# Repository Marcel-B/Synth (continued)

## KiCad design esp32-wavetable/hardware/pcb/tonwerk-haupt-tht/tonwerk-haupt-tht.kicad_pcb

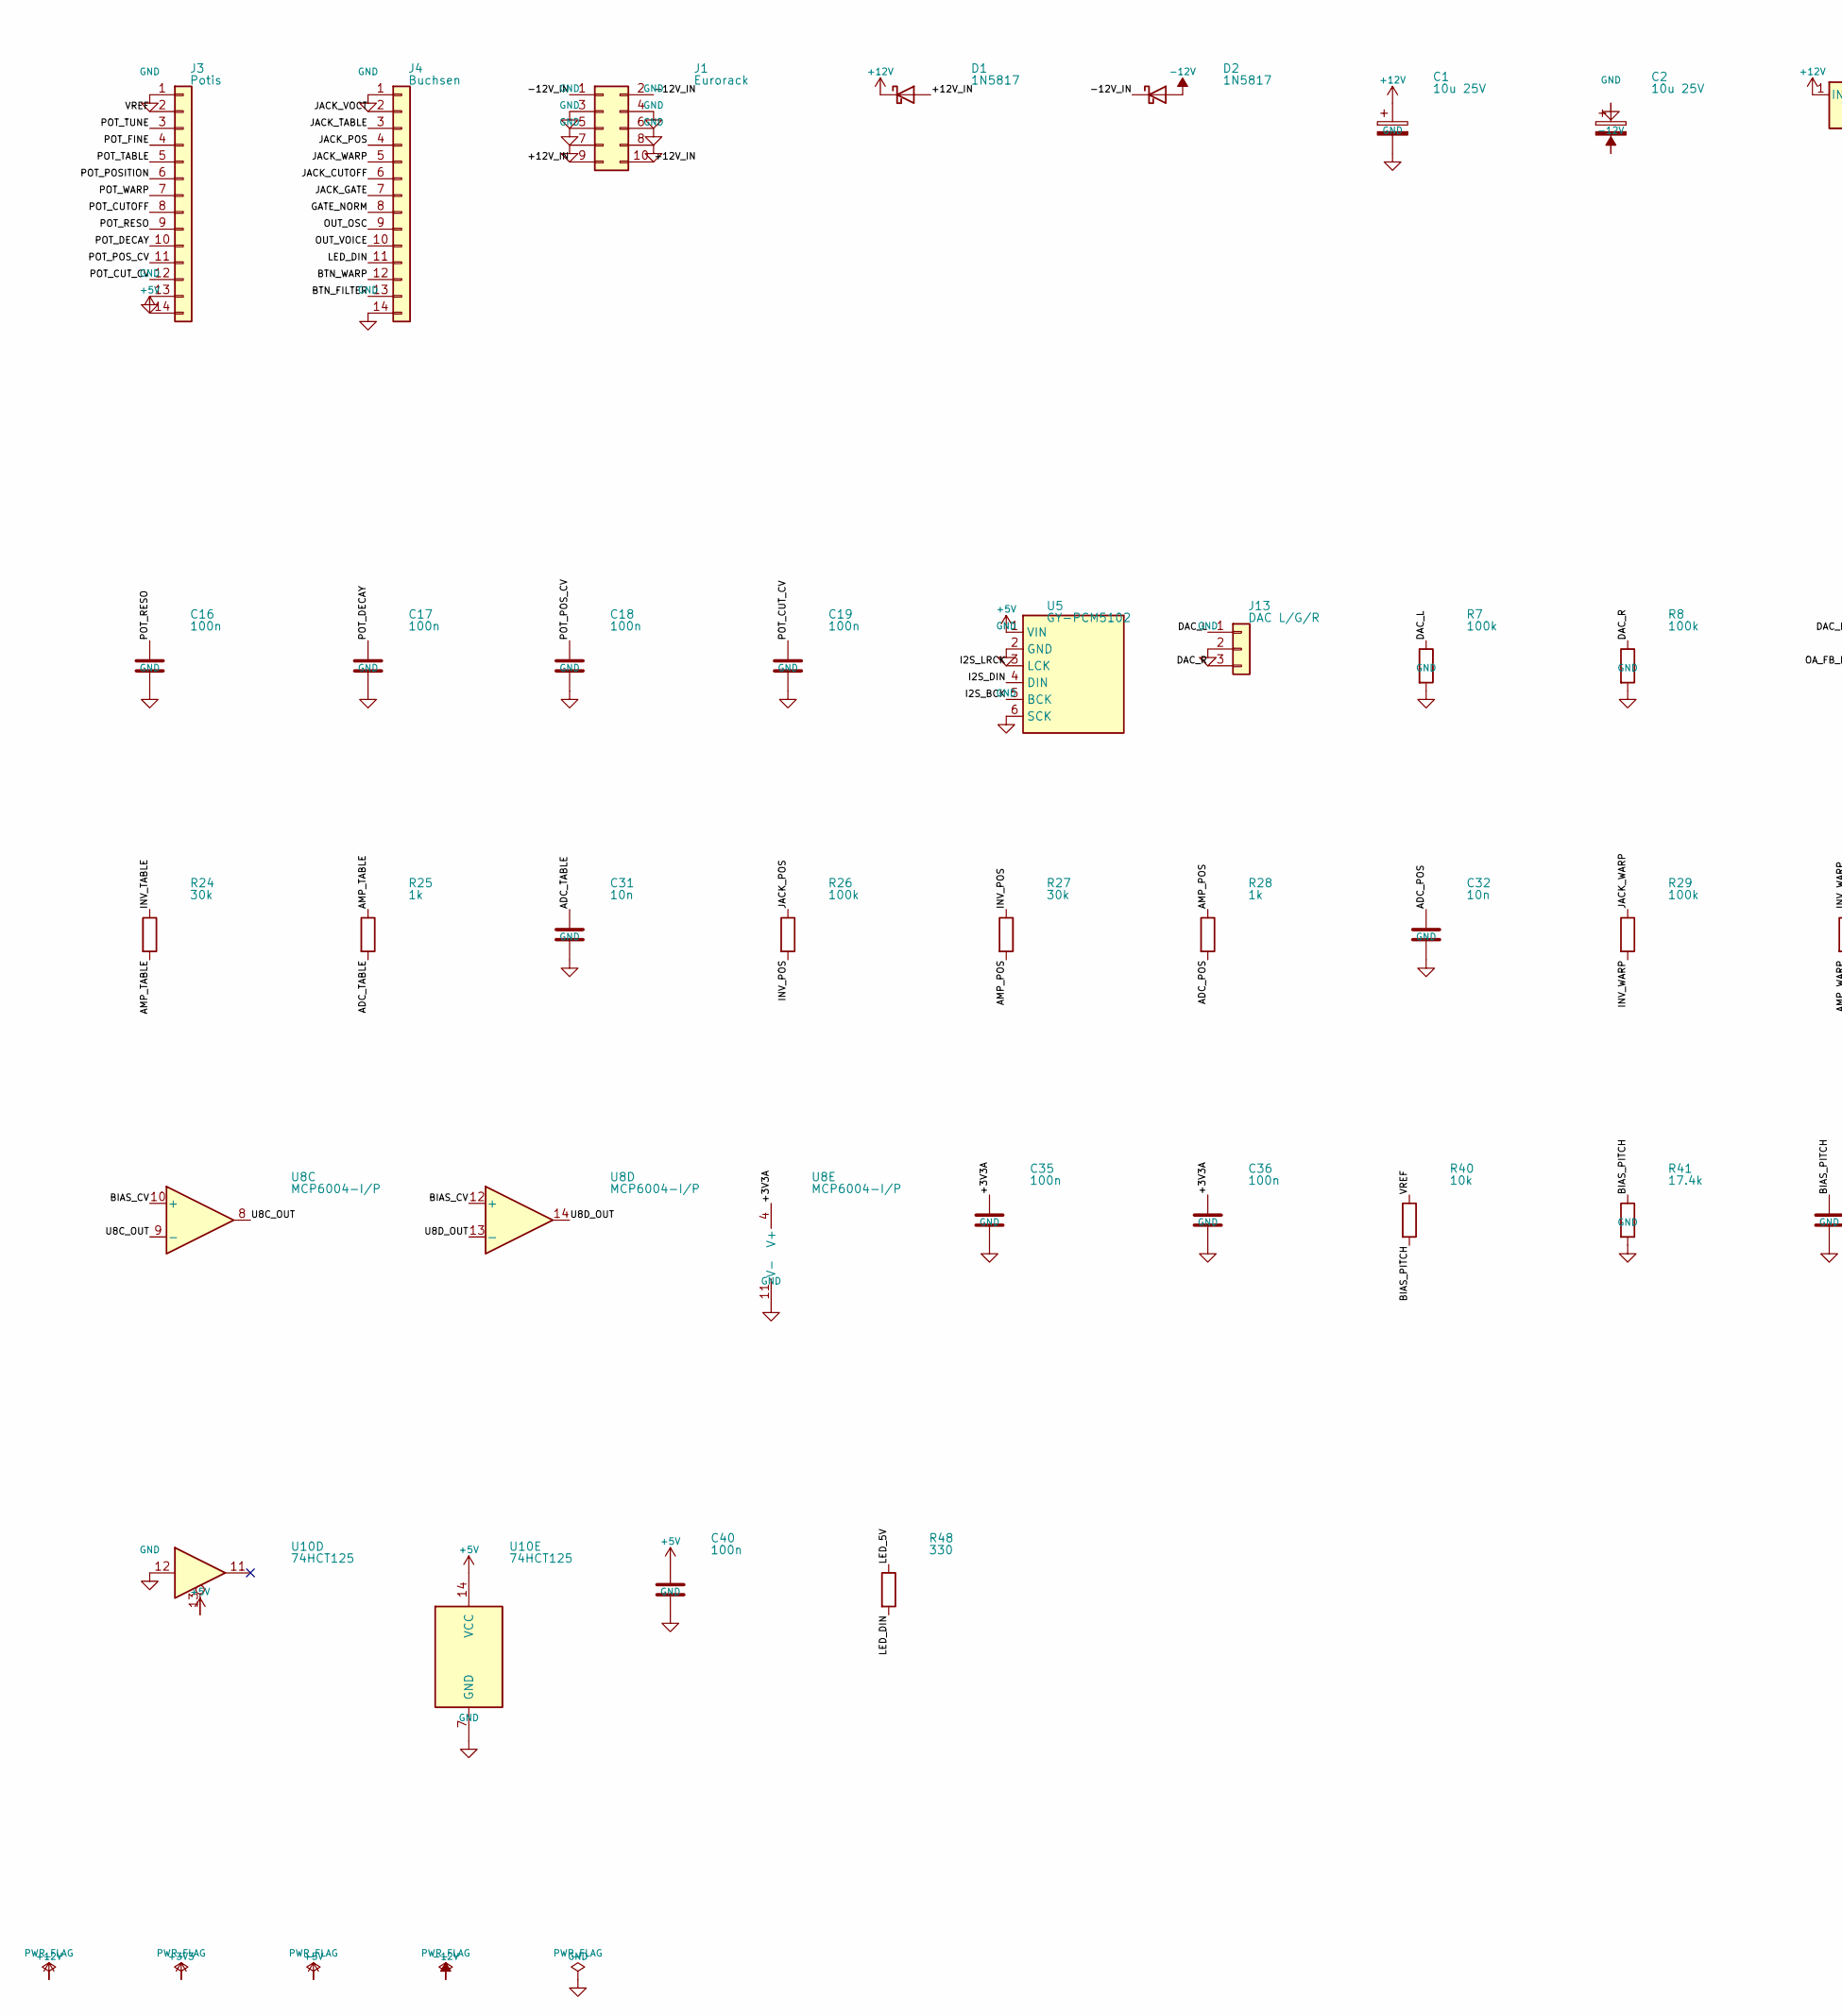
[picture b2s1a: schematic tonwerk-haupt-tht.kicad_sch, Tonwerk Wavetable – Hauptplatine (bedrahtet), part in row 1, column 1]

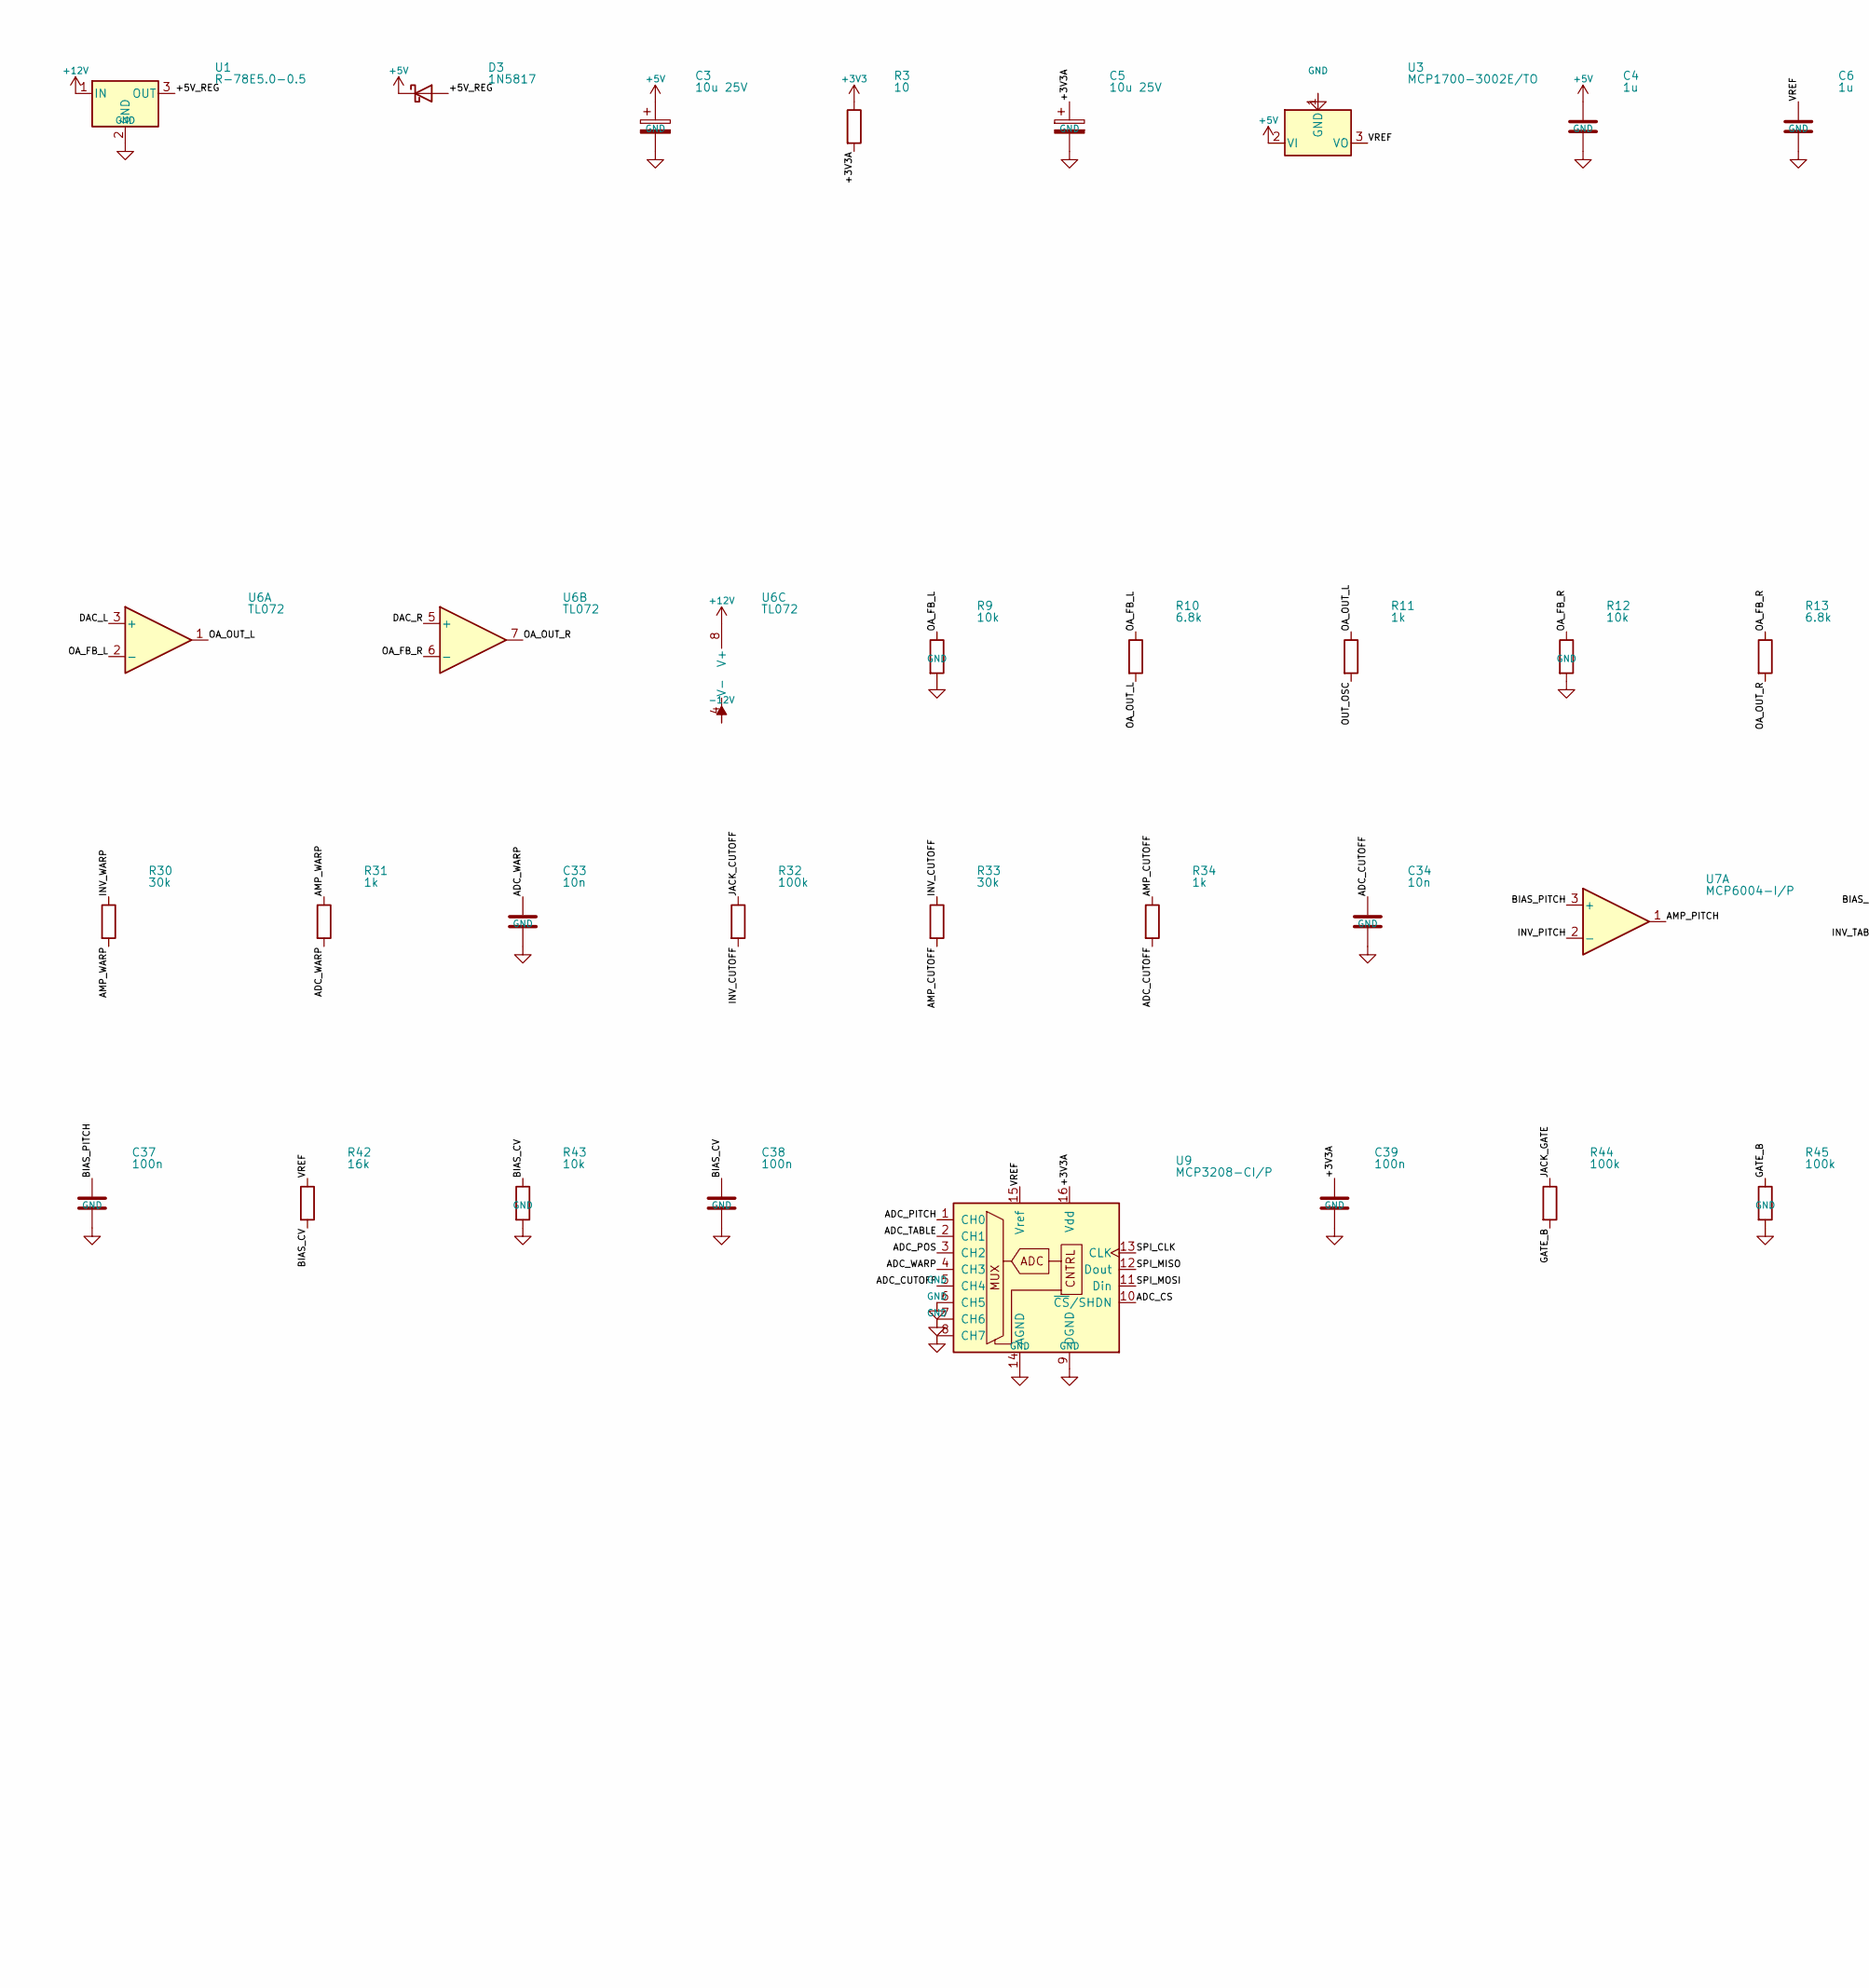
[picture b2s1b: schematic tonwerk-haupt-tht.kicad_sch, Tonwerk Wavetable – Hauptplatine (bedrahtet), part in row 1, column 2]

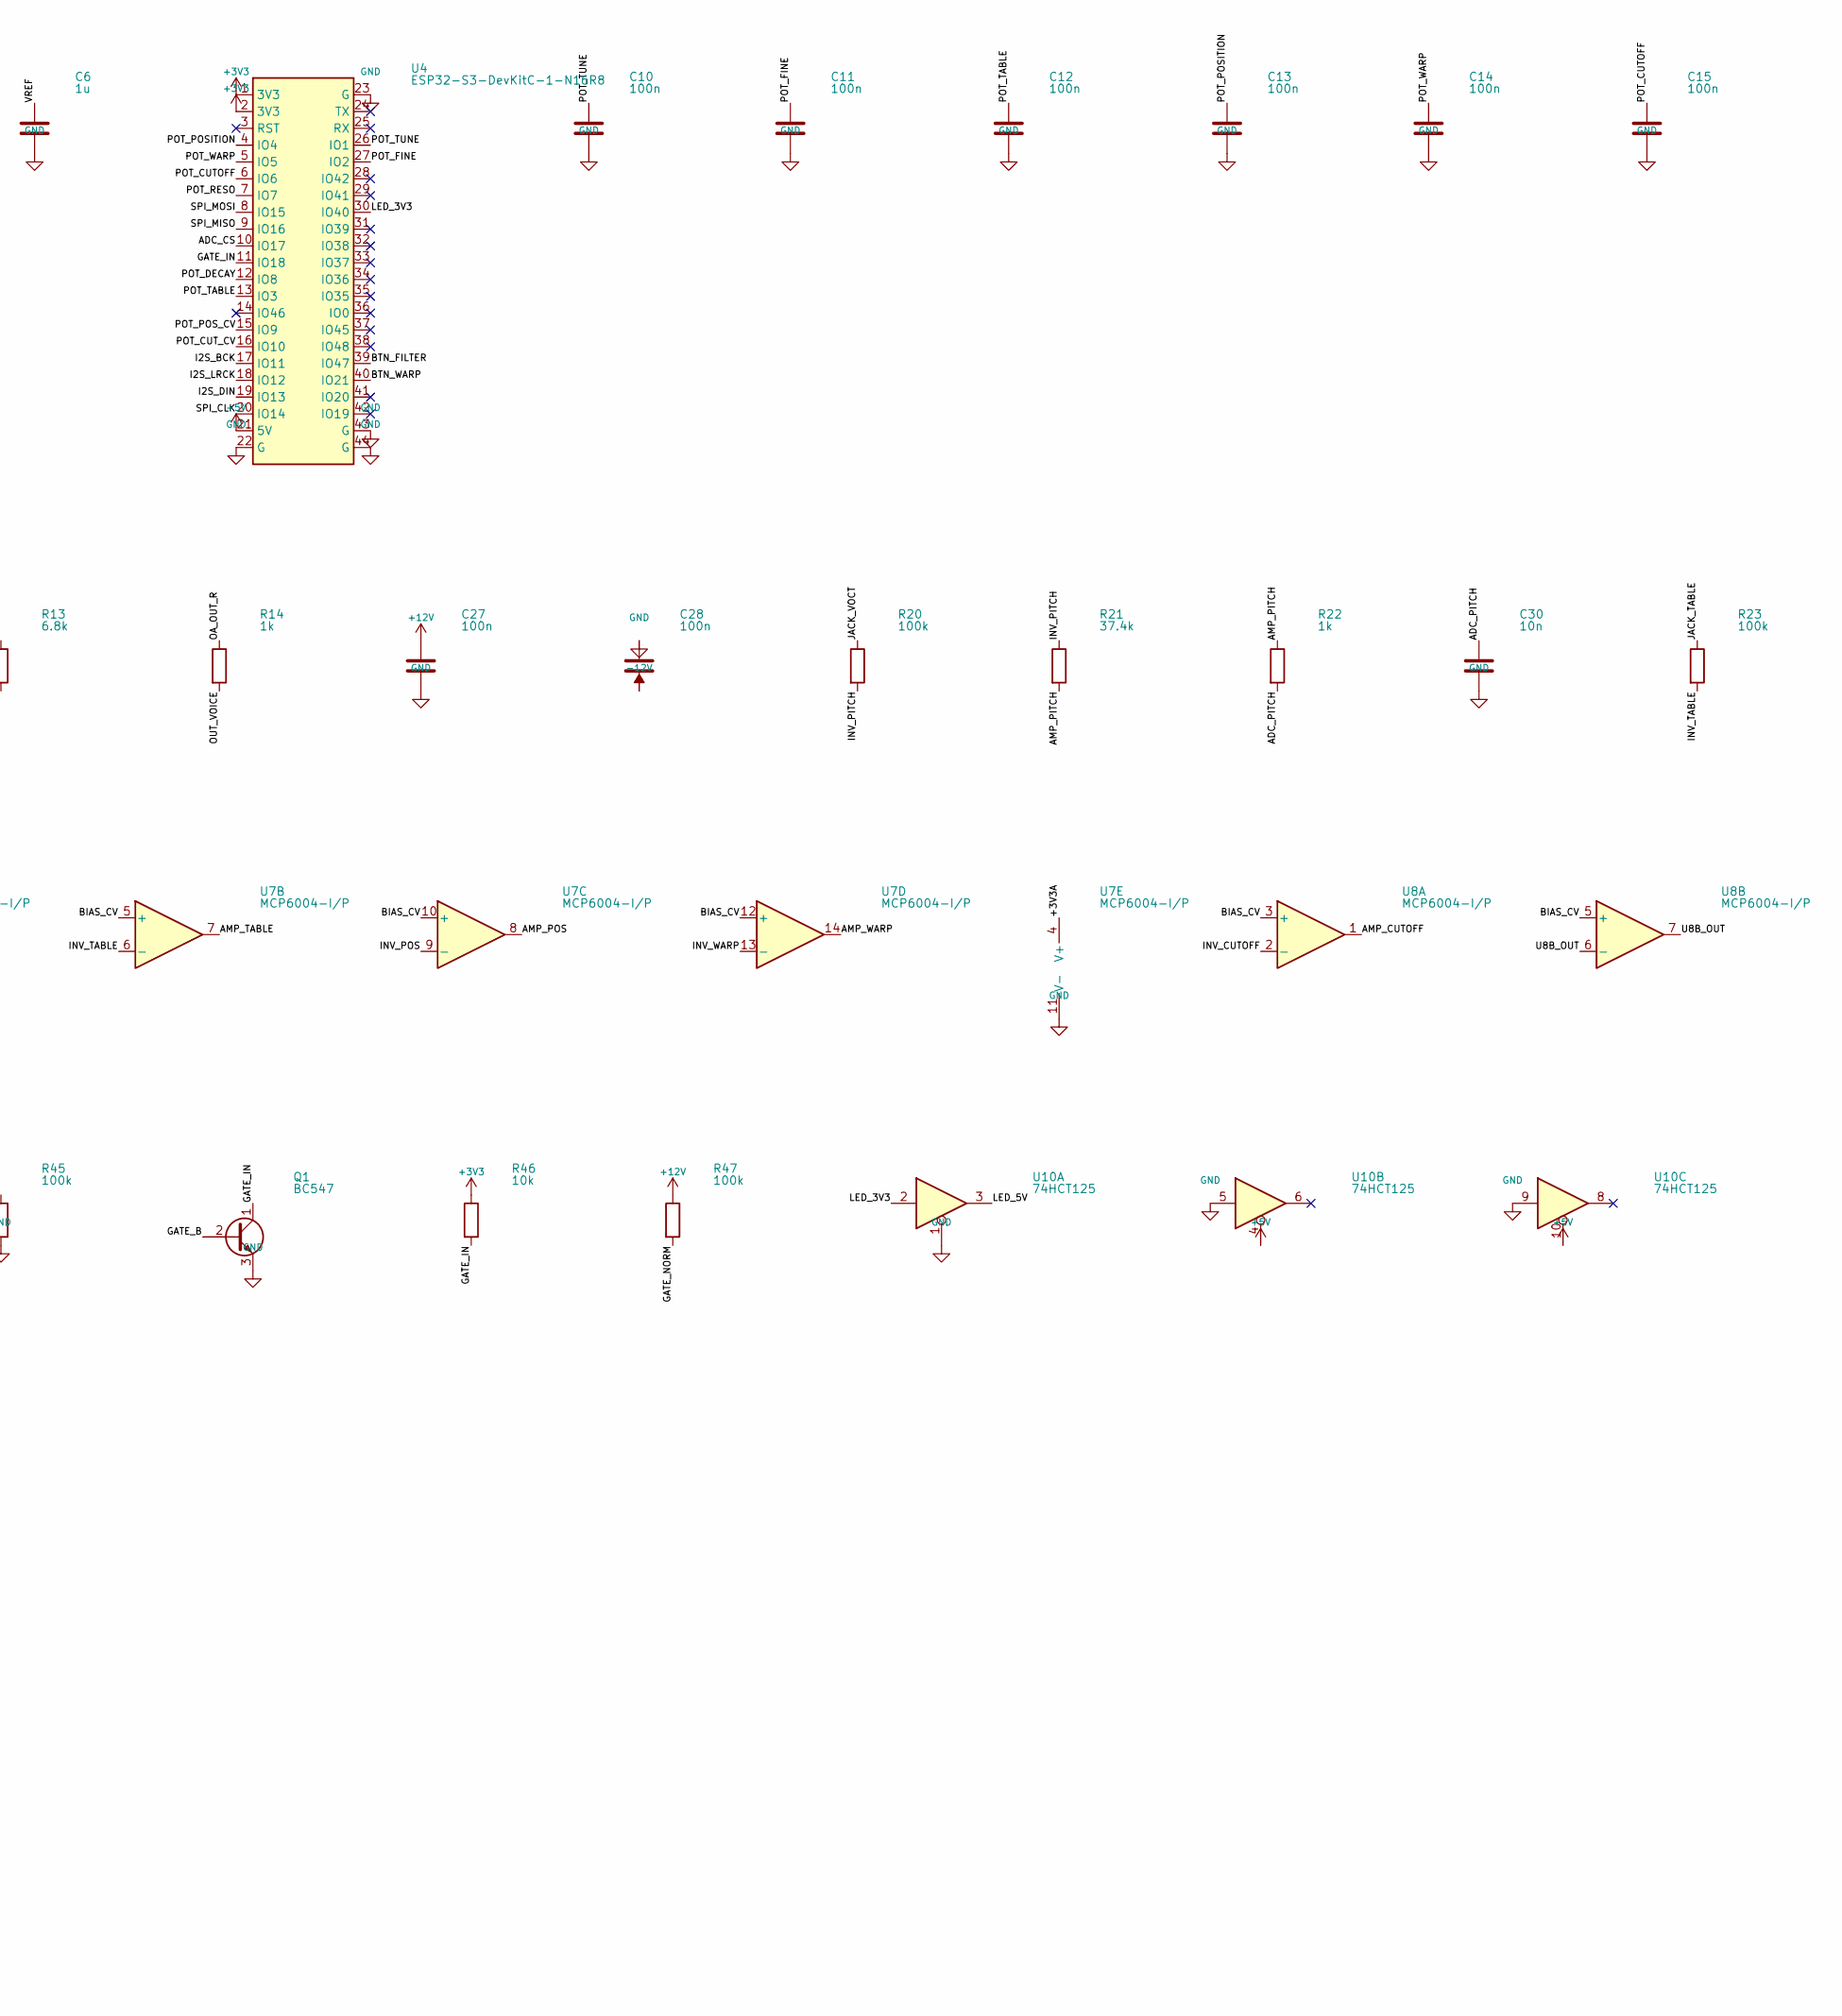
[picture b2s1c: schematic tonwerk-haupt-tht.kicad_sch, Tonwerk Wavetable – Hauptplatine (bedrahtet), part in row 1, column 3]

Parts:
C1, C2, C3, C5: 10u 25V; CP_Radial_D5.0mm_P2.00mm
C4, C6: 1u; C_Disc_D3.0mm_W2.0mm_P2.50mm
C10, C11, C12, C13, C14, C15, C16, C17, C18, C19, C27, C28, C35, C36, C37, C38, C39, C40: 100n; C_Disc_D3.0mm_W2.0mm_P2.50mm
C30, C31, C32, C33, C34: 10n; C_Disc_D3.0mm_W2.0mm_P2.50mm
D1, D2, D3: 1N5817; D_DO-41_SOD81_P10.16mm_Horizontal
J1: Eurorack; IDC-Header_2x05_P2.54mm_Vertical
J3: Potis; PinSocket_1x14_P2.54mm_Vertical
J4: Buchsen; PinSocket_1x14_P2.54mm_Vertical
J13: DAC L/G/R; PinHeader_1x03_P2.54mm_Vertical
Q1: BC547; TO-92_Inline
R3: 10; R_Axial_DIN0207_L6.3mm_D2.5mm_P10.16mm_Horizontal
R7, R8, R20, R23, R26, R29, R32, R44, R45, R47: 100k; R_Axial_DIN0207_L6.3mm_D2.5mm_P10.16mm_Horizontal
R9, R12, R40, R43, R46: 10k; R_Axial_DIN0207_L6.3mm_D2.5mm_P10.16mm_Horizontal
R10, R13: 6.8k; R_Axial_DIN0207_L6.3mm_D2.5mm_P10.16mm_Horizontal
R11, R14, R22, R25, R28, R31, R34: 1k; R_Axial_DIN0207_L6.3mm_D2.5mm_P10.16mm_Horizontal
R21: 37.4k; R_Axial_DIN0207_L6.3mm_D2.5mm_P10.16mm_Horizontal
R24, R27, R30, R33: 30k; R_Axial_DIN0207_L6.3mm_D2.5mm_P10.16mm_Horizontal
R41: 17.4k; R_Axial_DIN0207_L6.3mm_D2.5mm_P10.16mm_Horizontal
R42: 16k; R_Axial_DIN0207_L6.3mm_D2.5mm_P10.16mm_Horizontal
R48: 330; R_Axial_DIN0207_L6.3mm_D2.5mm_P10.16mm_Horizontal
U1: R-78E5.0-0.5; Converter_DCDC_RECOM_R-78E-0.5_THT
U3: MCP1700-3002E/TO; TO-92_Inline
U4: ESP32-S3-DevKitC-1-N16R8; ESP32-S3-DevKitC-1_Socket
U5: GY-PCM5102; GY-PCM5102_Socket
U6: TL072; DIP-8_W7.62mm
U7, U8: MCP6004-I/P; DIP-14_W7.62mm
U9: MCP3208-CI/P; DIP-16_W7.62mm
U10: 74HCT125; DIP-14_W7.62mm

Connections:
+3V3: R3.1, R46.1, U4.1 (3V3), U4.2 (3V3)
+3V3A: C5.1, C35.1, C36.1, C39.1, R3.2, U7.4 (V+), U8.4 (V+), U9.16 (Vdd)
+5V: C3.1, C4.1, C40.1, D3.1 (K), J3.14, U3.2 (VI), U4.21 (5V), U5.1 (VIN), U10.4, U10.10, U10.13, U10.14 (VCC)
+5V_REG: D3.2 (A), U1.3 (OUT)
+12V: C1.1, C27.1, D1.1 (K), R47.1, U1.1 (IN), U6.8 (V+)
+12V_IN: D1.2 (A), J1.9, J1.10
-12V: C2.2, C28.2, D2.2 (A), U6.4 (V-)
-12V_IN: D2.1 (K), J1.1, J1.2
ADC_CS: U4.10 (IO17), U9.10 (~CS/SHDN)
ADC_CUTOFF: C34.1, R34.2, U9.5 (CH4)
ADC_PITCH: C30.1, R22.2, U9.1 (CH0)
ADC_POS: C32.1, R28.2, U9.3 (CH2)
ADC_TABLE: C31.1, R25.2, U9.2 (CH1)
ADC_WARP: C33.1, R31.2, U9.4 (CH3)
AMP_CUTOFF: R33.2, R34.1, U8.1
AMP_PITCH: R21.2, R22.1, U7.1
AMP_POS: R27.2, R28.1, U7.8
AMP_TABLE: R24.2, R25.1, U7.7
AMP_WARP: R30.2, R31.1, U7.14
BIAS_CV: C38.1, R42.2, R43.1, U7.5 (+), U7.10 (+), U7.12 (+), U8.3 (+), U8.5 (+), U8.10 (+), U8.12 (+)
BIAS_PITCH: C37.1, R40.2, R41.1, U7.3 (+)
BTN_FILTER: J4.13, U4.39 (IO47)
BTN_WARP: J4.12, U4.40 (IO21)
DAC_L: J13.1, R7.1, U6.3 (+)
DAC_R: J13.3, R8.1, U6.5 (+)
GATE_B: Q1.2 (B), R44.2, R45.1
GATE_IN: Q1.1 (C), R46.2, U4.11 (IO18)
GATE_NORM: J4.8, R47.2
GND: C1.2, C2.1, C3.2, C4.2, C5.2, C6.2, C10.2, C11.2, C12.2, C13.2, C14.2, C15.2, C16.2, C17.2, C18.2, C19.2, C27.2, C28.1, C30.2, C31.2, C32.2, C33.2, C34.2, C35.2, C36.2, C37.2, C38.2, C39.2, C40.2, J1.3, J1.4, J1.5, J1.6, J1.7, J1.8, J3.1, J3.13, J4.1, J4.14, J13.2, Q1.3 (E), R7.2, R8.2, R9.2, R12.2, R41.2, R43.2, R45.2, U1.2 (GND), U3.1 (GND), U4.22 (G), U4.23 (G), U4.43 (G), U4.44 (G), U5.2 (GND), U5.6 (SCK), U7.11 (V-), U8.11 (V-), U9.6 (CH5), U9.7 (CH6), U9.8 (CH7), U9.9 (DGND), U9.14 (AGND), U10.1, U10.5, U10.7 (GND), U10.9, U10.12
I2S_BCK: U4.17 (IO11), U5.5 (BCK)
I2S_DIN: U4.19 (IO13), U5.4 (DIN)
I2S_LRCK: U4.18 (IO12), U5.3 (LCK)
INV_CUTOFF: R32.2, R33.1, U8.2 (-)
INV_PITCH: R20.2, R21.1, U7.2 (-)
INV_POS: R26.2, R27.1, U7.9 (-)
INV_TABLE: R23.2, R24.1, U7.6 (-)
INV_WARP: R29.2, R30.1, U7.13 (-)
JACK_CUTOFF: J4.6, R32.1
JACK_GATE: J4.7, R44.1
JACK_POS: J4.4, R26.1
JACK_TABLE: J4.3, R23.1
JACK_VOCT: J4.2, R20.1
JACK_WARP: J4.5, R29.1
LED_3V3: U4.30 (IO40), U10.2
LED_5V: R48.1, U10.3
LED_DIN: J4.11, R48.2
OA_FB_L: R9.1, R10.1, U6.2 (-)
OA_FB_R: R12.1, R13.1, U6.6 (-)
OA_OUT_L: R10.2, R11.1, U6.1
OA_OUT_R: R13.2, R14.1, U6.7
OUT_OSC: J4.9, R11.2
OUT_VOICE: J4.10, R14.2
POT_CUTOFF: C15.1, J3.8, U4.6 (IO6)
POT_CUT_CV: C19.1, J3.12, U4.16 (IO10)
POT_DECAY: C17.1, J3.10, U4.12 (IO8)
POT_FINE: C11.1, J3.4, U4.27 (IO2)
POT_POSITION: C13.1, J3.6, U4.4 (IO4)
POT_POS_CV: C18.1, J3.11, U4.15 (IO9)
POT_RESO: C16.1, J3.9, U4.7 (IO7)
POT_TABLE: C12.1, J3.5, U4.13 (IO3)
POT_TUNE: C10.1, J3.3, U4.26 (IO1)
POT_WARP: C14.1, J3.7, U4.5 (IO5)
SPI_CLK: U4.20 (IO14), U9.13 (CLK)
SPI_MISO: U4.9 (IO16), U9.12 (Dout)
SPI_MOSI: U4.8 (IO15), U9.11 (Din)
U8B_OUT: U8.6 (-), U8.7
U8C_OUT: U8.8, U8.9 (-)
U8D_OUT: U8.13 (-), U8.14
VREF: C6.1, J3.2, R40.1, R42.1, U3.3 (VO), U9.15 (Vref)

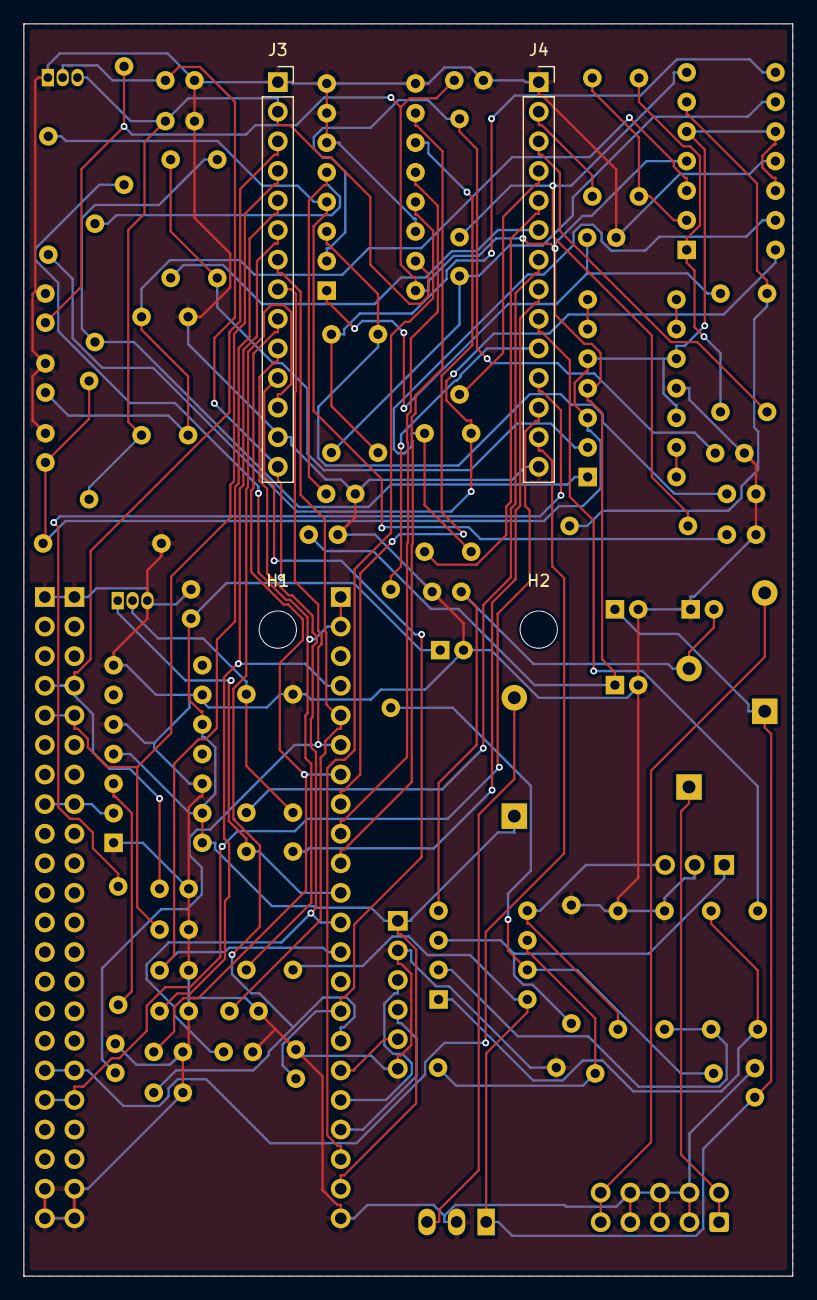
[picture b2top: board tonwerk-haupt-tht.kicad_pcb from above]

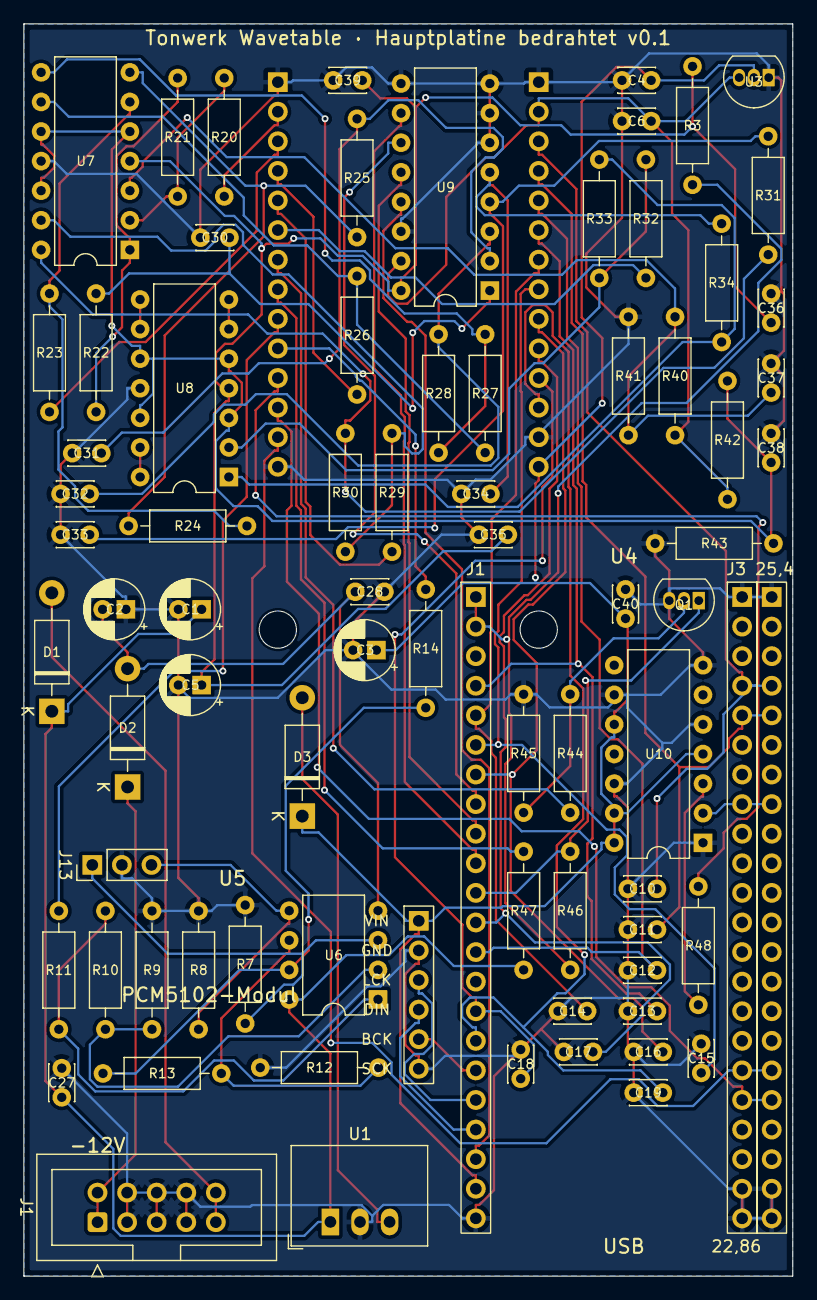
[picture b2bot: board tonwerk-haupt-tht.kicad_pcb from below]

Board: 2 copper layers, 66.0 x 107.5 mm, 81 parts (77 on the bottom side), 69 nets.

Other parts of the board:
H1, H2: M3; MountingHole_3.2mm_M3

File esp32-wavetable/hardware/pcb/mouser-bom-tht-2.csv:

Manufacturer Part Number,Quantity,Description,Designators
MCP3208-CI/P,1,ADC 12 bit 8 Kanäle DIP-16,U9
MCP6004-I/P,2,Op-Amp 4-fach Rail-to-Rail DIP-14,U7 U8
TL072CP,1,Op-Amp 2-fach DIP-8,U6
SN74HCT125N,1,Puffer 4-fach DIP-14,U10
MCP1700-3002E/TO,1,LDO 3.0 V TO-92 (Referenz),U3
BC547BTA,1,NPN TO-92,Q1
R-78E5.0-0.5,1,Schaltregler 12 V -> 5 V,U1
1N5817-E3/54,3,Schottky-Diode DO-41,D1 D2 D3
MFR-25FBF52-100K,10,Widerstand 100k 1 % 0207,R7 R8 R20 R23 R26 R29 R32 R44 R45 R47
MFR-25FBF52-1K,7,Widerstand 1k 1 % 0207,R11 R14 R22 R25 R28 R31 R34
MFR-25FBF52-10K,5,Widerstand 10k 1 % 0207,R9 R12 R40 R43 R46
MFR-25FBF52-30K,4,Widerstand 30k 1 % 0207,R24 R27 R30 R33
MFR-25FBF52-6K8,2,Widerstand 6.8k 1 % 0207,R10 R13
MFR-25FBF52-37K4,1,Widerstand 37.4k 1 % 0207,R21
MFR-25FBF52-17K4,1,Widerstand 17.4k 1 % 0207,R41
MFR-25FBF52-16K,1,Widerstand 16k 1 % 0207,R42
MFR-25FBF52-330R,1,Widerstand 330 Ohm 1 % 0207,R48
MFR-25FBF52-10R,1,Widerstand 10 Ohm 1 % 0207,R3
C315C104K5R5TA,20,Kerko 100 nF 50 V X7R RM 2.54 (18 Haupt + 2 Bedien),C10-C19 C27 C28 C35-C40; Bedien C1 C2
C315C103K5R5TA,5,Kerko 10 nF 50 V X7R RM 2.54,C30-C34
C315C105K3R5TA,2,Kerko 1 µF 25 V X7R RM 2.54,C4 C6
EEU-FC1H100L,4,Elko 10 µF 50 V 5 x 11 mm RM 2,C1 C2 C3 C5
110-43-314-41-001000,3,IC-Fassung DIP-14,U7 U8 U10
110-43-316-41-001000,1,IC-Fassung DIP-16,U9
110-43-308-41-001000,1,IC-Fassung DIP-8,U6
61303211821,2,Buchsenleiste 1x32 8.5 mm - auf 22 kürzen (DevKit),U4
61300611821,1,Buchsenleiste 1x6 8.5 mm (PCM-Modul),U5
61301611821,2,Buchsenleiste 1x16 8.5 mm - auf 14 kürzen,Haupt J3 J4
61301411121,2,Stiftleiste 1x14 gerade,Bedien J3 J4
61201021621,1,Wannenstecker 2x5 gerade (Eurorack),J1
